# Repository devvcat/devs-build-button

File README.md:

# devs-build-button
Developer's Build Button

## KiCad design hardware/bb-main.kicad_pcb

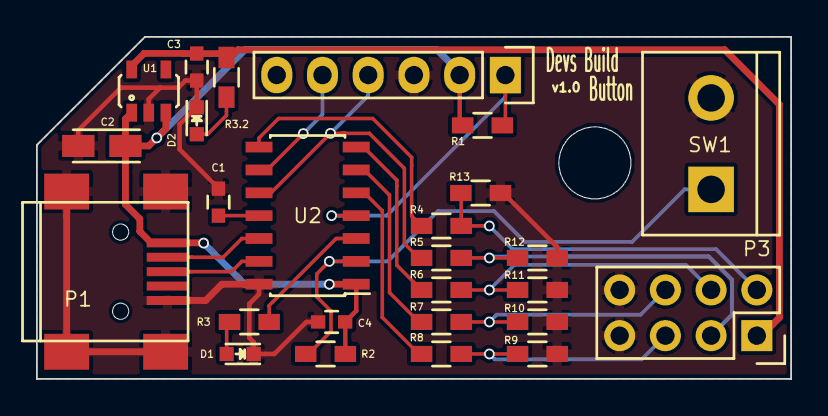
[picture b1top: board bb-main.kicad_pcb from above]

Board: 2 copper layers, 41.9 x 19.0 mm, 27 parts (0 on the bottom side), 22 nets.

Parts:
C1: 470nF; C_0603
C2: 10uF; TantalC_SizeA_EIA-3216_Reflow
C3, C4: 100nF; C_0603
D1, D2: Led_Small; LED_0603
MH1: MountingHole_4mm
P1: USB_B; USB_Mini-B
P2: PICkit3; Socket_Strip_Straight_1x06
P3: OLED; Socket_Strip_Straight_2x04
R1, R2: 10k; R_0603_HandSoldering
R3, R3.2: 390; R_0603_HandSoldering
R4, R5, R6, R7, R8: 8.2k; R_0603_HandSoldering
R9, R10, R11, R12, R13: 16k; R_0603_HandSoldering
SW1: SW_PUSH; bornier2
U1: BU33TD3WG-TR; SSOP5
U2: PIC16(L)F1455-I/SL; SOIC-14_3.9x8.7mm_Pitch1.27mm

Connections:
+3V3: C3.1, P3.1, R3.2.1, U1.5
+5V: C2.1, C4.1, P1.1, P2.2, R1.1, R2.1, U1.1, U1.3, U2.1
/BUT_1: R2.2, SW1.1, U2.2
/D/~C~: P3.4, R6.2, R11.2
/ICSPCLK: P2.5, U2.9
/ICSPDAT/OLED_SCK: P2.4, R5.1, U2.10
/LED_A: R3.1, U2.3
/OLED_D/~C~: R6.1, U2.7
/OLED_SDO: R4.1, U2.8
/OLED_~CS~: R7.1, U2.6
/OLED_~RES~: R8.1, U2.5
/SCK: P3.3, R5.2, R12.2
/SDO: P3.2, R4.2, R13.2
/~CS~: P3.6, R7.2, R10.2
/~MCLR~: P2.1, R1.2, U2.4
/~RES~: P3.5, R8.2, R9.2
GND: C1.1, C2.2, C3.2, C4.2, D1.1, D2.1, P1.5, P1.6, P2.3, P3.7, P3.8, R9.1, R10.1, R11.1, R12.1, R13.1, SW1.2, U1.2, U2.14
unnamed: C1.2, U2.11
unnamed: D1.2, R3.2
unnamed: D2.2, R3.2.2
unnamed: P1.2, U2.12
unnamed: P1.3, U2.13

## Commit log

2016-02-12 Added bb-main board schematic
2016-02-15 Created BU33TD3WG component
2016-02-15 Created SSOP-5 footprint
2016-02-15 Draw schematic components
2016-02-15 Added .gitignore
2016-02-17 Initial schematic revision
2016-02-19 Associate components footprint
2016-02-19 Fix ERC errors
2016-02-19 Fix BU33 LDO footprint
2016-02-19 Component footprints changed to 0603
2016-02-19 Add power LED
2016-02-19 Change button footprint
2016-02-19 Place components on the board
2016-02-19 Add power new class
2016-02-21 Board changes
2016-02-22 Board rework
2016-03-25 Board final rev 1.0
2016-04-09 Initial commit firmware
2016-04-09 Fix board unconnected track. Changed schematic USB connector.
